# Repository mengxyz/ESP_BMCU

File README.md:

#ESP BMCU

```text
bmcu port form ch32v203 to esp32s3 full web ui configuration
```

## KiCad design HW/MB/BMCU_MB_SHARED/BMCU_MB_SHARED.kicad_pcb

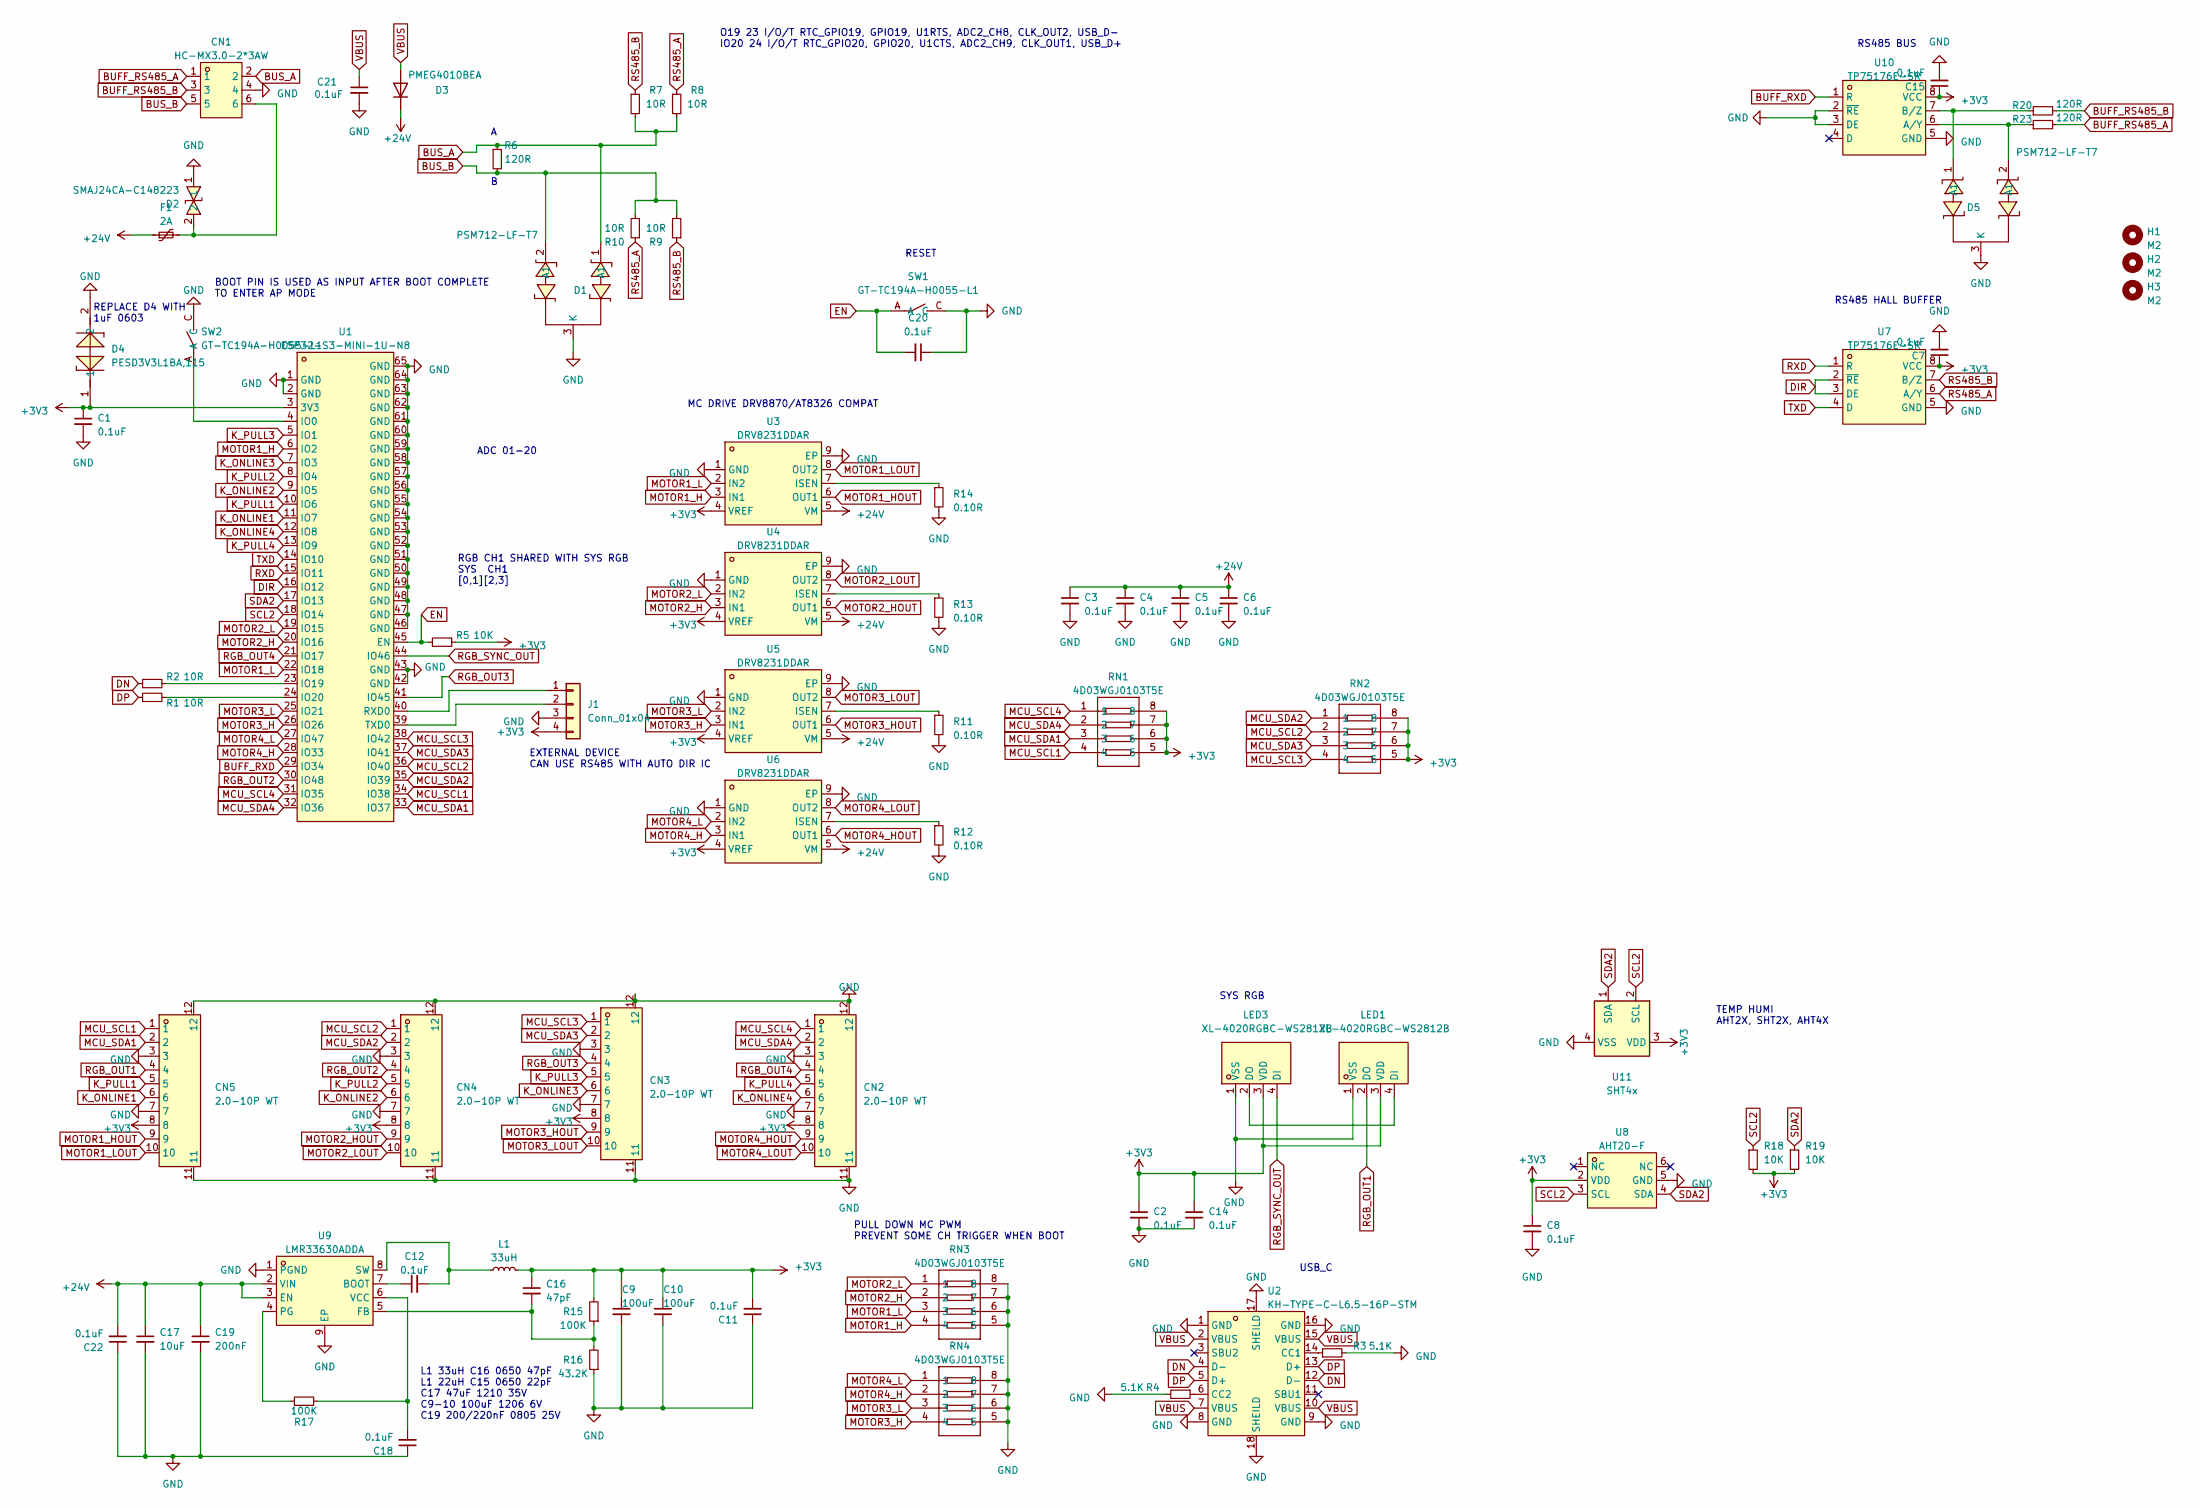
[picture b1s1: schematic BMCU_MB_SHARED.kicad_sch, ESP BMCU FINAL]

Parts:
C1, C2, C3, C4, C5, C6, C7, C8, C14, C15, C20, C21: 0.1uF; C_0603_1608Metric_Pad1.08x0.95mm_HandSolder
C9, C10: 100uF; C_1206_3216Metric
C11, C12, C18, C22: 0.1uF; C_0603_1608Metric
C16: 47pF; C_0603_1608Metric
C17: 10uF; C_1210_3225Metric
C19: 200nF; C_0805_2012Metric
CN1: HC-MX3.0-2*3AW; CONN-TH_6P-P3.00_HC-MX3.0-2X3AW_1; LCSC Part C3294384
CN2, CN3, CN4, CN5: 2.0-10P WT; CONN-SMD_10P-P2.00_2.0-10P-WT; LCSC Part C5340818
D1, D5: PSM712-LF-T7; SOT-23-3_L3.0-W1.7-P0.95-LS2.9-BR; LCSC Part C32677
D2: SMAJ24CA-C148223; SMA_L4.4-W2.6-LS5.0-BI; LCSC Part C148223
D3: PMEG4010BEA; D_SOD-323_HandSoldering
D4: PESD3V3L1BA,115; SOD-323_L1.7-W1.3-LS2.5-BI-1; LCSC Part C51450
F1: 2A; R_1812_4532Metric_Pad1.30x3.40mm_HandSolder
H1, H2, H3: M2; MountingHole_2.2mm_M2_DIN965
J1: Conn_01x04; PinHeader_1x04_P1.27mm_Vertical
L1: 33uH; L_Chilisin_BMRB00060650
LED1, LED3: XL-4020RGBC-WS2812B; LED-SMD_4P-L4.0-W1.7_XL-4020RGBC-WS2812B; LCSC Part C3647024
R1, R2, R7, R8, R9, R10: 10R; R_0603_1608Metric_Pad0.98x0.95mm_HandSolder
R3, R4: 5.1K; R_0603_1608Metric_Pad0.98x0.95mm_HandSolder
R5, R18, R19: 10K; R_0603_1608Metric_Pad0.98x0.95mm_HandSolder
R6, R20, R23: 120R; R_0603_1608Metric_Pad0.98x0.95mm_HandSolder
R11, R12, R13, R14: 0.10R; R_1210_3225Metric_Pad1.30x2.65mm_HandSolder
R15, R17: 100K; R_0603_1608Metric
R16: 43.2K; R_0603_1608Metric
RN1, RN2, RN3, RN4: 4D03WGJ0103T5E; RES-ARRAY-SMD_0603-8P-L3.2-W1.6-BL; LCSC Part C29718
SW1, SW2: GT-TC194A-H0055-L1; SW-SMD_4P-L2.5-W1.6-LS2.9_STI-055A12AX; MPN GT-TC194A-H0055-L1; LCSC Part C41398745
U1: ESP32-S3-MINI-1U-N8; BULETM-SMD_ESPRESSIF_ESP32-S3-MINI-1U-N8; LCSC Part C2980299
U2: KH-TYPE-C-L6.5-16P-STM; USB-SMD_KH-TYPE-C-L6.5-16P-STM; LCSC Part C2919639
U3, U4, U5, U6: DRV8231DDAR; HSOP-8_L5.0-W4.0-P1.27-LS6.2-BL-EP; LCSC Part C5218850
U7, U10: TP75176E-SR; SOP-8_L4.9-W3.9-P1.27-LS6.0-BL; LCSC Part C94207
U8: AHT20-F; SENSOR-SMD-6_AHT20; LCSC Part C3012622
U9: LMR33630ADDA; ESOP-8_L4.9-W3.9-P1.27-LS6.0-BL-EP-1; MPN LMR33630ADDA; LCSC Part C2866787
U11: SHT4x; Sensirion_DFN-4_1.5x1.5mm_P0.8mm_SHT4x_NoCentralPad

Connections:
+3V3: C1.1, C2.1, C7.1, C8.1, C9.1, C10.1, C11.2, C14.1, C15.1, C16.1, CN2.8, CN3.8, CN4.8, CN5.8, D4.1, J1.4, L1.2, LED1.3 (VDD), LED3.3 (VDD), R5.2, R15.2, R18.2, R19.2, RN1.5, RN1.6, RN1.7, RN1.8, RN2.5, RN2.6, RN2.7, RN2.8, U1.3 (3V3), U3.4 (VREF), U4.4 (VREF), U5.4 (VREF), U6.4 (VREF), U7.8 (VCC), U8.2 (VDD), U10.8 (VCC), U11.3 (VDD)
+24V: C3.1, C4.1, C5.1, C6.1, C17.1, C19.1, C22.2, D3.1 (K), F1.1, U3.5 (VM), U4.5 (VM), U5.5 (VM), U6.5 (VM), U9.2 (VIN), U9.3 (EN)
BUFF_RS485_A: CN1.1, R23.2
BUFF_RS485_B: CN1.3, R20.2
BUFF_RXD: U1.29 (IO34), U10.1 (R)
BUS_A: CN1.2, D1.1 (A1), R6.1, R7.2, R8.2
BUS_B: CN1.5, D1.2 (A1), R6.2, R9.2, R10.2
DIR: U1.16 (IO12), U7.2 (~RE), U7.3 (DE)
DN: R2.1, U2.4 (D-), U2.12 (D-)
DP: R1.1, U2.5 (D+), U2.13 (D+)
EN: C20.2, R5.1, SW1.A, U1.45 (EN)
GND: C1.2, C2.2, C3.2, C4.2, C5.2, C6.2, C7.2, C8.2, C9.2, C10.2, C11.1, C14.2, C15.2, C17.2, C18.1, C19.2, C20.1, C21.2, C22.1, CN1.4, CN2.3, CN2.7, CN2.11, CN2.12, CN3.3, CN3.7, CN3.11, CN3.12, CN4.3, CN4.7, CN4.11, CN4.12, CN5.3, CN5.7, CN5.11, CN5.12, D1.3 (K), D2.1, D4.2, D5.3 (K), J1.3, LED1.1 (VSS), LED3.1 (VSS), R3.2, R4.2, R11.2, R12.2, R13.2, R14.2, R16.1, RN3.5, RN3.6, RN3.7, RN3.8, RN4.5, RN4.6, RN4.7, RN4.8, SW1.C, SW2.C, U1.1 (GND), U1.2 (GND), U1.42 (GND), U1.43 (GND), U1.46 (GND), U1.47 (GND), U1.48 (GND), U1.49 (GND), U1.50 (GND), U1.51 (GND), U1.52 (GND), U1.53 (GND), U1.54 (GND), U1.55 (GND), U1.56 (GND), U1.57 (GND), U1.58 (GND), U1.59 (GND), U1.60 (GND), U1.61 (GND), U1.62 (GND), U1.63 (GND), U1.64 (GND), U1.65 (GND), U2.1 (GND), U2.8 (GND), U2.9 (GND), U2.16 (GND), U2.17 (SHEILD), U2.18 (SHEILD), U3.1 (GND), U3.9 (EP), U4.1 (GND), U4.9 (EP), U5.1 (GND), U5.9 (EP), U6.1 (GND), U6.9 (EP), U7.5 (GND), U8.5 (GND), U9.1 (PGND), U9.9 (EP), U10.2 (~RE), U10.3 (DE), U10.5 (GND), U11.4 (VSS)
K_ONLINE1: CN5.6, U1.11 (IO7)
K_ONLINE2: CN4.6, U1.9 (IO5)
K_ONLINE3: CN3.6, U1.7 (IO3)
K_ONLINE4: CN2.6, U1.12 (IO8)
K_PULL1: CN5.5, U1.10 (IO6)
K_PULL2: CN4.5, U1.8 (IO4)
K_PULL3: CN3.5, U1.5 (IO1)
K_PULL4: CN2.5, U1.13 (IO9)
MCU_SCL1: CN5.1, RN1.4, U1.34 (IO38)
MCU_SCL2: CN4.1, RN2.2, U1.36 (IO40)
MCU_SCL3: CN3.1, RN2.4, U1.38 (IO42)
MCU_SCL4: CN2.1, RN1.1, U1.31 (IO35)
MCU_SDA1: CN5.2, RN1.3, U1.33 (IO37)
MCU_SDA2: CN4.2, RN2.1, U1.35 (IO39)
MCU_SDA3: CN3.2, RN2.3, U1.37 (IO41)
MCU_SDA4: CN2.2, RN1.2, U1.32 (IO36)
MOTOR1_H: RN3.4, U1.6 (IO2), U3.3 (IN1)
MOTOR1_HOUT: CN5.9, U3.6 (OUT1)
MOTOR1_L: RN3.3, U1.22 (IO18), U3.2 (IN2)
MOTOR1_LOUT: CN5.10, U3.8 (OUT2)
MOTOR2_H: RN3.2, U1.20 (IO16), U4.3 (IN1)
MOTOR2_HOUT: CN4.9, U4.6 (OUT1)
MOTOR2_L: RN3.1, U1.19 (IO15), U4.2 (IN2)
MOTOR2_LOUT: CN4.10, U4.8 (OUT2)
MOTOR3_H: RN4.4, U1.26 (IO26), U5.3 (IN1)
MOTOR3_HOUT: CN3.9, U5.6 (OUT1)
MOTOR3_L: RN4.3, U1.25 (IO21), U5.2 (IN2)
MOTOR3_LOUT: CN3.10, U5.8 (OUT2)
MOTOR4_H: RN4.2, U1.28 (IO33), U6.3 (IN1)
MOTOR4_HOUT: CN2.9, U6.6 (OUT1)
MOTOR4_L: RN4.1, U1.27 (IO47), U6.2 (IN2)
MOTOR4_LOUT: CN2.10, U6.8 (OUT2)
unnamed: CN1.6, D2.2, F1.2
unnamed: J1.1, U1.40 (RXD0)
unnamed: J1.2, U1.39 (TXD0)
unnamed: LED1.4 (DI), LED3.2 (DO)
unnamed: SW2.A, U1.4 (IO0)
unnamed: R2.2, U1.23 (IO19)
unnamed: R1.2, U1.24 (IO20)
unnamed: R3.1, U2.14 (CC1)
unnamed: R4.1, U2.6 (CC2)
unnamed: R14.1, U3.7 (ISEN)
unnamed: R13.1, U4.7 (ISEN)
unnamed: R11.1, U5.7 (ISEN)
unnamed: R12.1, U6.7 (ISEN)
unnamed: C12.1, U9.7 (BOOT)
unnamed: C16.2, R15.1, R16.2, U9.5 (FB)
unnamed: R17.1, U9.4 (PG)
unnamed: C12.2, L1.1, U9.8 (SW)
unnamed: C18.2, R17.2, U9.6 (VCC)
unnamed: D5.2 (A1), R23.1, U10.6 (A/Y)
unnamed: D5.1 (A1), R20.1, U10.7 (B/Z)
RGB_OUT1: CN5.4, LED1.2 (DO)
RGB_OUT2: CN4.4, U1.30 (IO48)
RGB_OUT3: CN3.4, U1.41 (IO45)
RGB_OUT4: CN2.4, U1.21 (IO17)
RGB_SYNC_OUT: LED3.4 (DI), U1.44 (IO46)
RS485_A: R8.1, R10.1, U7.6 (A/Y)
RS485_B: R7.1, R9.1, U7.7 (B/Z)
RXD: U1.15 (IO11), U7.1 (R)
SCL2: R18.1, U1.18 (IO14), U8.3 (SCL), U11.2 (SCL)
SDA2: R19.1, U1.17 (IO13), U8.4 (SDA), U11.1 (SDA)
TXD: U1.14 (IO10), U7.4 (D)
VBUS: C21.1, D3.2 (A), U2.2 (VBUS), U2.7 (VBUS), U2.10 (VBUS), U2.15 (VBUS)

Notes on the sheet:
REPLACE D4 WITH 1uF 0603
MC DRIVE DRV8870/AT8326 COMPAT
ADC 01-20
BOOT PIN IS USED AS INPUT AFTER BOOT COMPLETE TO ENTER AP MODE
RS485 HALL BUFFER
RS485 BUS
L1 33uH C16 0650 47pF L1 22uH C15 0650 22pF C17 47uF 1210 35V C9-10 100uF 1206 6V C19 200/220nF 0805 25V
PULL DOWN MC PWM PREVENT SOME CH TRIGGER WHEN BOOT
EXTERNAL DEVICE CAN USE RS485 WITH AUTO DIR IC
USB_C
RESET
SYS RGB
O19 23 I/O/T RTC_GPIO19, GPIO19, U1RTS, ADC2_CH8, CLK_OUT2, USB_D- IO20 24 I/O/T RTC_GPIO20, GPIO20, U1CTS, ADC2_CH9, CLK_OUT1, USB_D+
RGB CH1 SHARED WITH SYS RGB SYS CH1 [0,1][2,3]
TEMP HUMI AHT2X, SHT2X, AHT4X

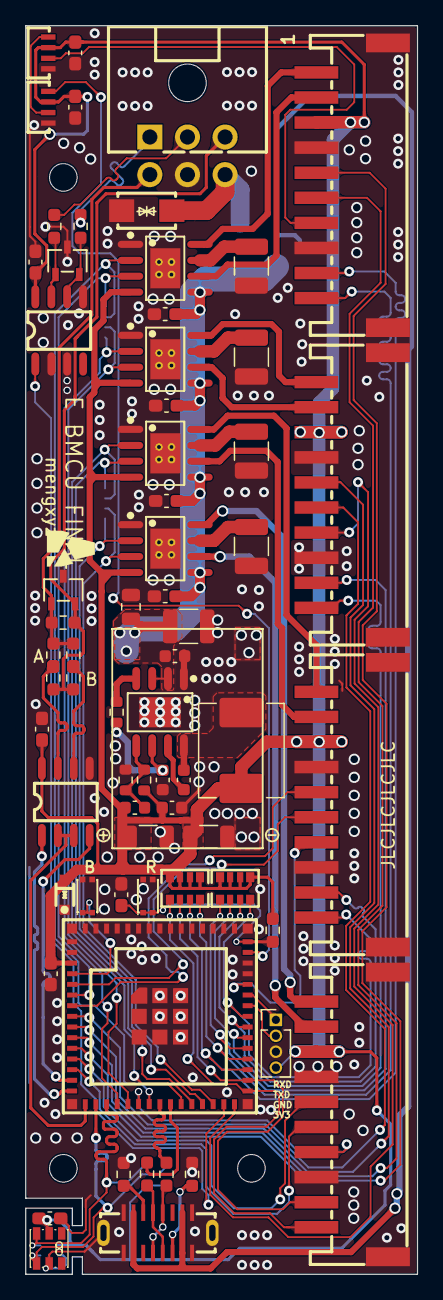
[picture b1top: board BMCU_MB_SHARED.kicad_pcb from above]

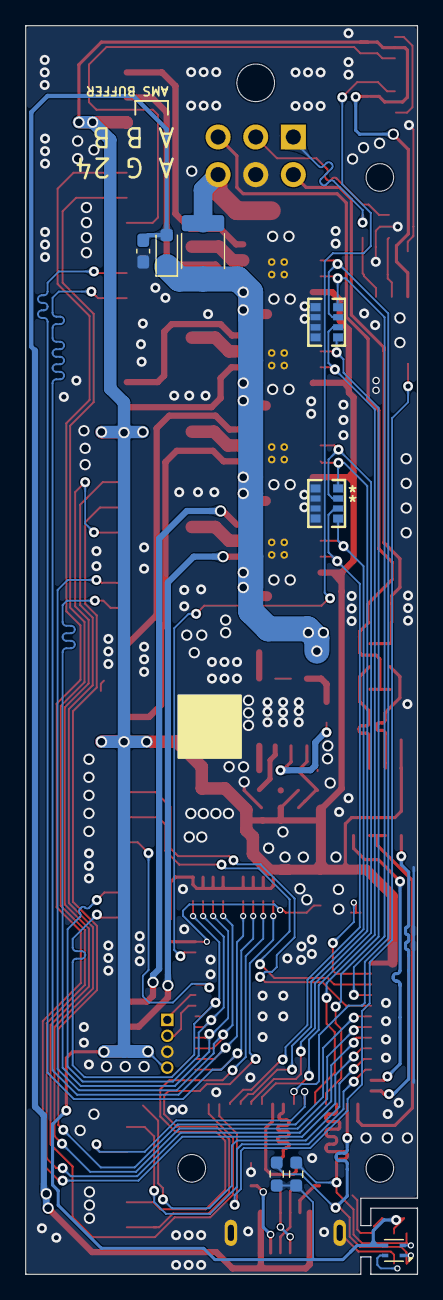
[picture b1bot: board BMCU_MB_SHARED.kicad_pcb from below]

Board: 2 copper layers, 31.2 x 99.6 mm, 77 parts (8 on the bottom side), 76 nets.

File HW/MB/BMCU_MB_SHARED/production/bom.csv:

Designator,Footprint,Quantity,Value,LCSC Part #
"C1, C11, C12, C14, C15, C18, C2, C20, C21, C22, C3, C4, C5, C6, C7, C8",0603,16,0.1uF,
"C10, C9",1206,2,100uF,
C16,0603,1,47pF,
C17,1210,1,10uF,
C19,0805,1,200nF,
CN1,CONN-TH_6P-P3.00_HC-MX3.0-2X3AW_1,1,HC-MX3.0-2*3AW,C3294384
"CN2, CN3, CN4, CN5",CONN-SMD_10P-P2.00_2.0-10P-WT,4,2.0-10P WT,C5340818
"D1, D5",SOT-23-3_L3.0-W1.7-P0.95-LS2.9-BR,2,PSM712-LF-T7,C32677
D2,SMA_L4.4-W2.6-LS5.0-BI,1,SMAJ24CA-C148223,C148223
D3,D_SOD-323_HandSoldering,1,1N4148WS,
D4,SOD-323_L1.7-W1.3-LS2.5-BI-1,1,"PESD3V3L1BA,115",C51450
F1,1812,1,2A,
"H1, H2, H3",MountingHole_2.2mm_M2_DIN965,3,M2,
J1,PinHeader_1x04_P1.27mm_Vertical,1,Conn_01x04,
L1,L_Chilisin_BMRB00060650,1,33uH,
"LED1, LED3",LED-SMD_4P-L4.0-W1.7_XL-4020RGBC-WS2812B,2,XL-4020RGBC-WS2812B,C3647024
"R1, R10, R2, R7, R8, R9",0603,6,10R,
"R11, R12, R13, R14",1210,4,0.10R,
"R15, R17",0603,2,100K,
R16,0603,1,43.2K,
"R18, R19, R5",0603,3,10K,
"R20, R23, R6",0603,3,120R,
"R3, R4",0603,2,5.1K,
"RN1, RN2, RN3, RN4",RES-ARRAY-SMD_0603-8P-L3.2-W1.6-BL,4,4D03WGJ0103T5E,C29718
"SW1, SW2",SW-SMD_4P-L2.5-W1.6-LS2.9_STI-055A12AX,2,GT-TC194A-H0055-L1,C41398745
U1,BULETM-SMD_ESPRESSIF_ESP32-S3-MINI-1U-N8,1,ESP32-S3-MINI-1U-N8,C2980299
"U10, U7",SOP-8_L4.9-W3.9-P1.27-LS6.0-BL,2,TP75176E-SR,C94207
U11,Sensirion_DFN-4_1.5x1.5mm_P0.8mm_SHT4x_NoCentralPad,1,SHT4x,
U2,USB-SMD_KH-TYPE-C-L6.5-16P-STM,1,KH-TYPE-C-L6.5-16P-STM,C2919639
"U3, U4, U5, U6",HSOP-8_L5.0-W4.0-P1.27-LS6.2-BL-EP,4,DRV8231DDAR,C5218850
U8,SENSOR-SMD-6_AHT20,1,AHT20-F,C3012622
U9,ESOP-8_L4.9-W3.9-P1.27-LS6.0-BL-EP-1,1,LMR33630ADDA,C2866787
